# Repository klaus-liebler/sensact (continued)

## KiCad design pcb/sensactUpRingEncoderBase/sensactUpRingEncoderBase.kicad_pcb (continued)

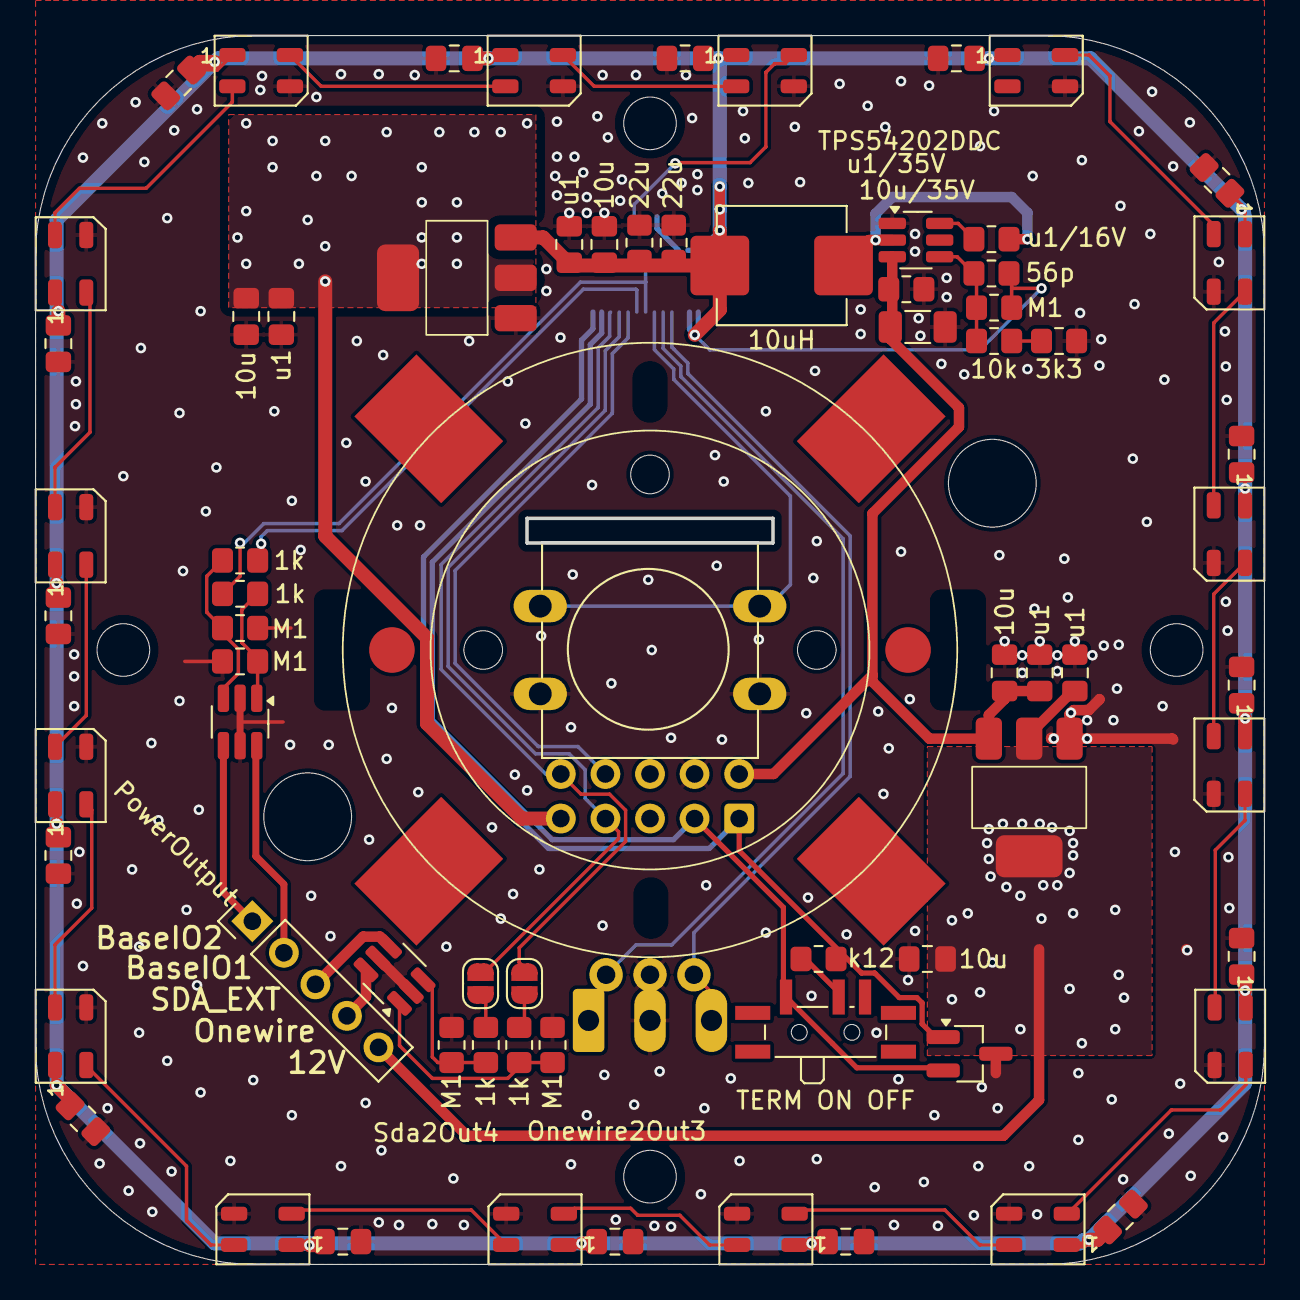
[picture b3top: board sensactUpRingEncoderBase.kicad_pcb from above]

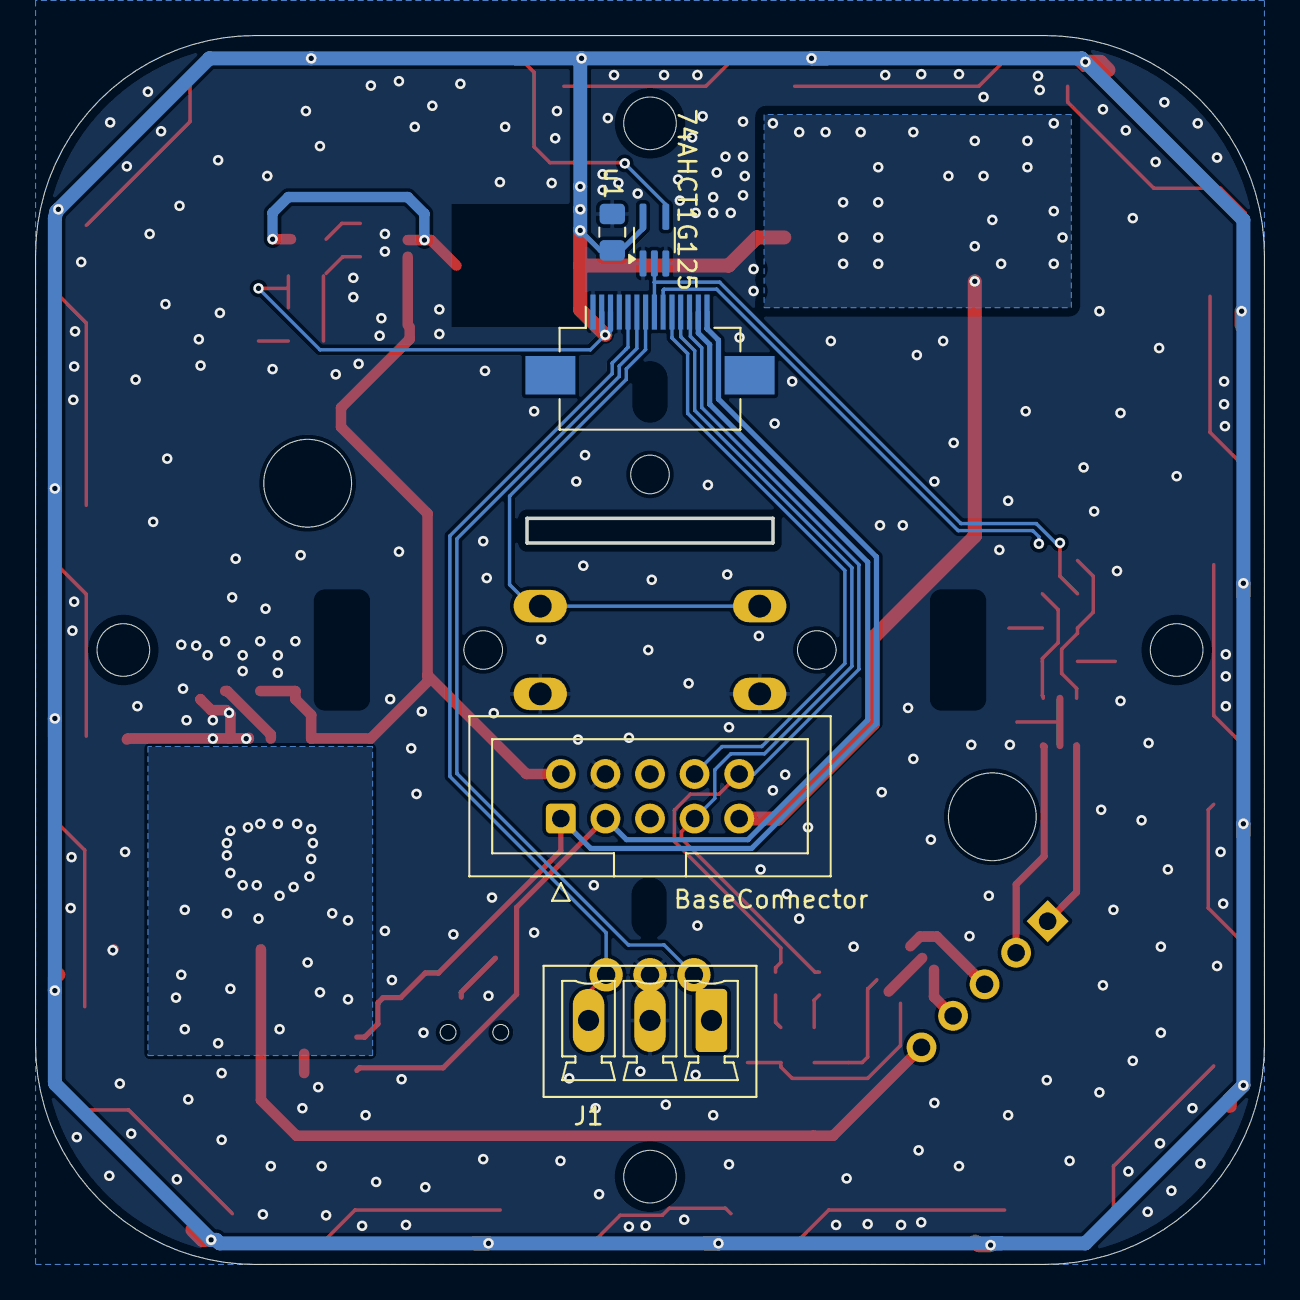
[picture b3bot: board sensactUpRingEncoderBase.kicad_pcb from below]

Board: 2 copper layers, 70.0 x 70.0 mm, 81 parts (5 on the bottom side), 46 nets.

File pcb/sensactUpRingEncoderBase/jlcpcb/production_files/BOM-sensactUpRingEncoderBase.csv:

Comment,Designator,Footprint,LCSC,Quantity
AMS1117-12,U7,SOT-223-3_TabPin2_HANDSOLDER,,1
ROT_EXT,J1,"PhoenixContact_MCV_1,5_3-G-3.5_1x03_P3.50mm_Vertical_smallerCourtyard",,1
10u,C55,C_0805_2012Metric_Pad1.18x1.45mm_HandSolder,,1
u1,C54,C_0805_2012Metric_Pad1.18x1.45mm_HandSolder,,1
u1,C53,C_0805_2012Metric_Pad1.18x1.45mm_HandSolder,,1
10u,C48,C_0805_2012Metric_Pad1.18x1.45mm_HandSolder,,1
BaseConnector,J3,IDC-Header_2x05_P2.54mm_Vertical,,1
AMS1117-3.3,U4,SOT-223-3_TabPin2_HANDSOLDER,,1
M1,R61,R_0805_2012Metric_Pad1.20x1.40mm_HandSolder,,1
M1,R62,R_0805_2012Metric_Pad1.20x1.40mm_HandSolder,,1
MountingHole,H5,MountingHole_2.2mm_M2,,1
SW_Push,SW1,Button_12mm_ANCHOR_CENTER,,1
u1,C15,C_0805_2012Metric_Pad1.18x1.45mm_HandSolder,,1
M1,R64,R_0805_2012Metric_Pad1.20x1.40mm_HandSolder,,1
u1,C20,C_0805_2012Metric_Pad1.18x1.45mm_HandSolder,,1
TERM ON OFF,SW2,SW_SPDT_PCM12_handsolder,,1
NUP2105L,D1,SOT-23_Handsoldering,,1
WS2812B,D6,LED_WS2812B-Mini_PLCC4_3.5x3.5mm,,1
MountingHole,H4,MountingHole_2.2mm_M2,,1
WS2812B,D12,LED_WS2812B-Mini_PLCC4_3.5x3.5mm,,1
MountingHole,H1,MountingHole_5mm,,1
WS2812B,D7,LED_WS2812B-Mini_PLCC4_3.5x3.5mm,,1
u1,C22,C_0805_2012Metric_Pad1.18x1.45mm_HandSolder,,1
WS2812B,D13,LED_WS2812B-Mini_PLCC4_3.5x3.5mm,,1
u1,C17,C_0805_2012Metric_Pad1.18x1.45mm_HandSolder,,1
u1/16V,C81,R_0805_2012Metric_Pad1.20x1.40mm_HandSolder,,1
u1/35V,C79,R_0805_2012Metric_Pad1.20x1.40mm_HandSolder,,1
k12,R1,R_0805_2012Metric_Pad1.20x1.40mm_HandSolder,,1
M1,R63,R_0805_2012Metric_Pad1.20x1.40mm_HandSolder,,1
3k3,R49,R_0805_2012Metric_Pad1.20x1.40mm_HandSolder,,1
WS2812B,D15,LED_WS2812B-Mini_PLCC4_3.5x3.5mm,,1
WS2812B,D4,LED_WS2812B-Mini_PLCC4_3.5x3.5mm,,1
u1,C23,C_0805_2012Metric_Pad1.18x1.45mm_HandSolder,,1
u1,C24,C_0805_2012Metric_Pad1.18x1.45mm_HandSolder,,1
WS2812B,D14,LED_WS2812B-Mini_PLCC4_3.5x3.5mm,,1
u1,C16,C_0805_2012Metric_Pad1.18x1.45mm_HandSolder,,1
1k,R57,R_0805_2012Metric_Pad1.20x1.40mm_HandSolder,,1
u1,C28,C_0805_2012Metric_Pad1.18x1.45mm_HandSolder,,1
22u,C84,R_0805_2012Metric_Pad1.20x1.40mm_HandSolder,,1
AO6800-HXY,Q3,SOT-23-6_Handsoldering,,1
WS2812B,D10,LED_WS2812B-Mini_PLCC4_3.5x3.5mm,,1
u1,C26,C_0805_2012Metric_Pad1.18x1.45mm_HandSolder,,1
PowerOutput,J7,PinHeader_1x05_P2.54mm_Vertical,,1
u1,C27,C_0805_2012Metric_Pad1.18x1.45mm_HandSolder,,1
WS2812B,D5,LED_WS2812B-Mini_PLCC4_3.5x3.5mm,,1
10u,C12,C_0805_2012Metric_Pad1.18x1.45mm_HandSolder,,1
u1,C29,C_0805_2012Metric_Pad1.18x1.45mm_HandSolder,,1
WS2812B,D16,LED_WS2812B-Mini_PLCC4_3.5x3.5mm,,1
MountingHole,H2,MountingHole_5mm,,1
WS2812B,D17,LED_WS2812B-Mini_PLCC4_3.5x3.5mm,,1
10uH,L4,L_0630,,1
WS2812B,D9,LED_WS2812B-Mini_PLCC4_3.5x3.5mm,,1
MountingHole,H3,MountingHole_2.2mm_M2,,1
u1,C10,C_0805_2012Metric_Pad1.18x1.45mm_HandSolder,,1
WS2812B,D8,LED_WS2812B-Mini_PLCC4_3.5x3.5mm,,1
56p,C82,R_0805_2012Metric_Pad1.20x1.40mm_HandSolder,,1
u1,C21,C_0805_2012Metric_Pad1.18x1.45mm_HandSolder,,1
WS2812B,D2,LED_WS2812B-Mini_PLCC4_3.5x3.5mm,,1
10u/35V,C80,C_1206_3216Metric_Pad1.33x1.80mm_HandSolder,,1
AO6800-HXY,Q2,SOT-23-6_Handsoldering,,1
WS2812B,D3,LED_WS2812B-Mini_PLCC4_3.5x3.5mm,,1
10u,C9,C_0805_2012Metric_Pad1.18x1.45mm_HandSolder,,1
u1,C11,C_0805_2012Metric_Pad1.18x1.45mm_HandSolder,,1
u1,C18,C_0805_2012Metric_Pad1.18x1.45mm_HandSolder,,1
WS2812B,D11,LED_WS2812B-Mini_PLCC4_3.5x3.5mm,,1
u1,C14,C_0805_2012Metric_Pad1.18x1.45mm_HandSolder,,1
10k,R60,R_0805_2012Metric_Pad1.20x1.40mm_HandSolder,,1
22u,C83,R_0805_2012Metric_Pad1.20x1.40mm_HandSolder,,1
1k,R56,R_0805_2012Metric_Pad1.20x1.40mm_HandSolder,,1
M1,R59,R_0805_2012Metric_Pad1.20x1.40mm_HandSolder,,1
u1,C19,C_0805_2012Metric_Pad1.18x1.45mm_HandSolder,,1
1k,R58,R_0805_2012Metric_Pad1.20x1.40mm_HandSolder,,1
TPS54202DDC,U27,SOT-23-6_Handsoldering,,1
1k,R55,R_0805_2012Metric_Pad1.20x1.40mm_HandSolder,,1
RotaryEncoder,SW3,Encoder Alps-Alpine EC35,,1
u1,C25,C_0805_2012Metric_Pad1.18x1.45mm_HandSolder,,1
u1,C13,C_0805_2012Metric_Pad1.18x1.45mm_HandSolder,,1
ToBase,J5,Hirose_FH12-14S-0.5SH_1x14-1MP_P0.50mm_Horizontal_handsolder,,1
74AHCT1G125,U5,SOT-353_SC-70-5_Handsoldering,,1

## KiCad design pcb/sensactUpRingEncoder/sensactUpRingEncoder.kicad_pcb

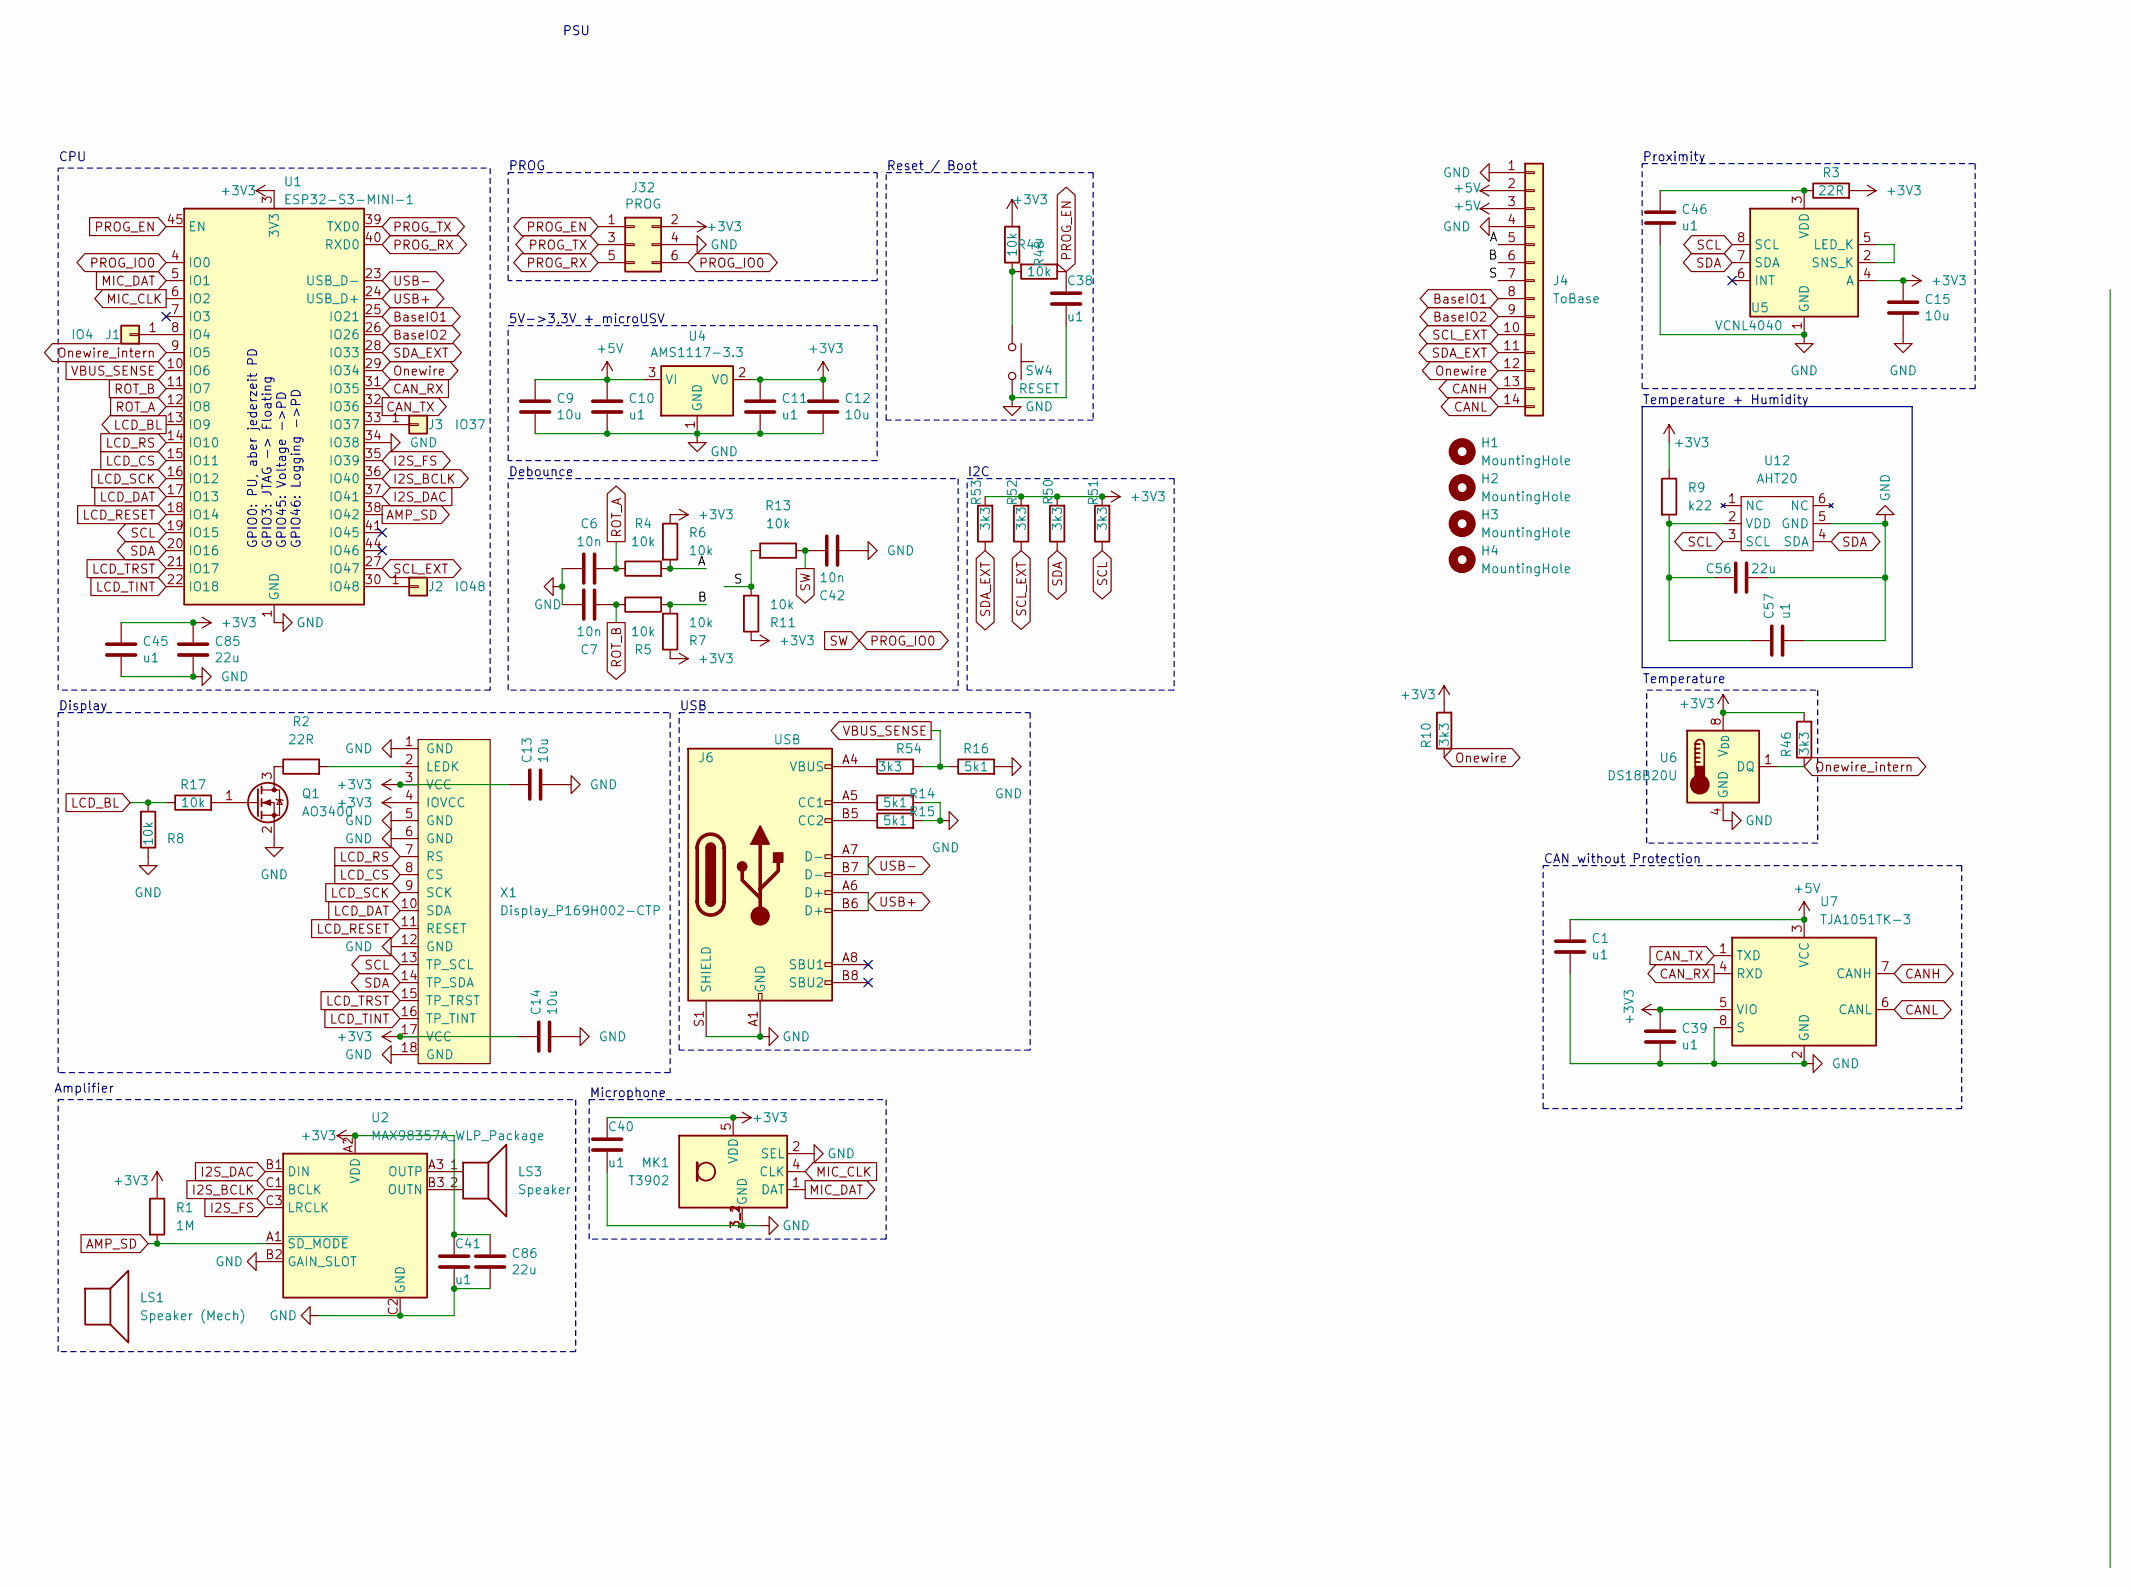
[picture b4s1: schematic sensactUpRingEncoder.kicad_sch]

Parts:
C1, C10, C11, C38, C39, C40, C41, C45, C46: u1; C_0201_0603Metric
C6, C7, C42: 10n; C_0201_0603Metric
C9, C12, C13, C14, C15: 10u; C_0402_1005Metric
C56, C85, C86: 22u; C_0603_1608Metric; MPN CL10A226MP8NUNE
C57: u1; C_0201_0603Metric; MPN GRM033R61A104KE15D
H1, H2, H3, H4: MountingHole; MountingHole_2.2mm_M2_DIN965
J1: IO4; TestPoint_THTPad_D1.0mm_Drill0.5mm
J2: IO48; TestPoint_THTPad_D1.5mm_Drill0.7mm
J3: IO37; TestPoint_THTPad_D1.5mm_Drill0.7mm
J4: ToBase; Hirose_FH12-14S-0.5SH_1x14-1MP_P0.50mm_Horizontal
J6: USB; USB_C_Receptacle_HRO_TYPE-C-31-M-12
J32: PROG; PinHeader_2x03_P1.27mm_Vertical_SMD
LS1: Speaker (Mech); SPEAKER_2415
LS3: Speaker; PinHeader_1x02_P1.27mm_Vertical
MK1: T3902; MIC_T3902
Q1: AO3400; SOT-23_smaller
R1: 1M; R_0805_2012Metric_Pad1.20x1.40mm_HandSolder
R2, R3: 22R; R_0805_2012Metric
R4, R5, R6, R7, R8, R11, R13, R17, R47, R48: 10k; R_0201_0603Metric
R9: k22; R_0805_2012Metric_Pad1.20x1.40mm_HandSolder; MPN 0402WGF2200TCE
R10, R46: 3k3; R_0402_1005Metric
R14, R15, R16: 5k1; R_0402_1005Metric
R50, R51, R52, R53, R54: 3k3; R_0402_1005Metric; MPN 0402WGF3301TCE
SW4: RESET; SW_Push_SPST_NO_4x3x2_handsolder
U1: ESP32-S3-MINI-1
U2: MAX98357A_WLP_Package; Maxim_WLP-9_1.595x1.415_Layout3x3_P0.4mm_Ball0.27mm_Pad0.25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
U4: AMS1117-3.3; SOT-223-3_TabPin2
U5: VCNL4040; VCNL4040_handsolder
U6: DS18B20U; MSOP-8_3x3mm_P0.65mm_handsolder
U7: TJA1051TK-3; HVSON-8-1EP_3x3mm_P0.65mm_EP1.6x2.4mm
U12: AHT20; AHT21; MPN AHT20
X1: Display_P169H002-CTP

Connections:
+3V3: C11.1, C12.1, C13.1, C14.1, C15.1, C39.1, C40.1, C41.1, C45.1, C85.1, C86.1, J32.2, MK1.5 (VDD), R1.1, R3.2, R6.1, R7.1, R9.1, R10.2, R11.1, R46.2, R47.2, R50.2, R51.2, R52.2, R53.2, U1.3 (3V3), U2.A2 (VDD), U4.2 (VO), U5.4 (A), U6.8 (V_{DD}), U7.5 (VIO), X1.3 (VCC), X1.4 (IOVCC), X1.17 (VCC)
+5V: C1.1, C9.1, C10.1, J4.2, J4.3, U4.3 (VI), U7.3 (VCC)
/A: J4.5, R4.2, R6.2
/B: J4.6, R5.2, R7.2
/S: J4.7, R11.2, R13.2
AMP_SD: R1.2, U1.38 (IO42), U2.A1 (~SD_MODE)
BaseIO1: J4.8, U1.25 (IO21)
BaseIO2: J4.9, U1.26 (IO26)
CANH: J4.13, U7.7 (CANH)
CANL: J4.14, U7.6 (CANL)
CAN_RX: U1.31 (IO35), U7.4 (RXD)
CAN_TX: U1.32 (IO36), U7.1 (TXD)
GND: C1.2, C6.1, C7.1, C9.2, C10.2, C11.2, C12.2, C13.2, C14.2, C15.2, C38.2, C39.2, C40.2, C41.2, C42.2, C45.2, C46.2, C56.2, C57.1, C85.2, C86.2, J4.1, J4.4, J6.A1 (GND), J6.A12 (GND), J6.B1 (GND), J6.B12 (GND), J6.S1 (SHIELD), J32.4, MK1.2 (SEL), MK1.3_1 (GND), MK1.3_2 (GND), Q1.2 (S), R8.1, R14.2, R15.2, R16.2, SW4.2, U1.1 (GND), U1.2 (GND), U1.34 (IO38), U1.42 (GND), U1.43 (GND), U1.46 (GND), U1.47 (GND), U1.48 (GND), U1.49 (GND), U1.50 (GND), U1.51 (GND), U1.52 (GND), U1.53 (GND), U1.54 (GND), U1.55 (GND), U1.56 (GND), U1.57 (GND), U1.58 (GND), U1.59 (GND), U1.60 (GND), U1.61 (GND), U1.62 (GND), U1.63 (GND), U1.64 (GND), U1.65 (GND), U2.B2 (GAIN_SLOT), U2.C2 (GND), U4.1 (GND), U5.1 (GND), U6.4 (GND), U7.2 (GND), U7.8 (S), U7.9 (GND), U12.5 (GND), X1.1 (GND), X1.5 (GND), X1.6 (GND), X1.12 (GND), X1.18 (GND)
I2S_BCLK: U1.36 (IO40), U2.C1 (BCLK)
I2S_DAC: U1.37 (IO41), U2.B1 (DIN)
I2S_FS: U1.35 (IO39), U2.C3 (LRCLK)
LCD_BL: R8.2, R17.1, U1.13 (IO9)
LCD_CS: U1.15 (IO11), X1.8 (CS)
LCD_DAT: U1.17 (IO13), X1.10 (SDA)
LCD_RESET: U1.18 (IO14), X1.11 (RESET)
LCD_RS: U1.14 (IO10), X1.7 (RS)
LCD_SCK: U1.16 (IO12), X1.9 (SCK)
LCD_TINT: U1.22 (IO18), X1.16 (TP_TINT)
LCD_TRST: U1.21 (IO17), X1.15 (TP_TRST)
MIC_CLK: MK1.4 (CLK), U1.6 (IO2)
MIC_DAT: MK1.1 (DAT), U1.5 (IO1)
unnamed: J1.1, U1.8 (IO4)
unnamed: J2.1, U1.30 (IO48)
unnamed: J3.1, U1.33 (IO37)
unnamed: J6.A5 (CC1), R14.1
unnamed: J6.B5 (CC2), R15.1
unnamed: J6.A4 (VBUS), J6.A9 (VBUS), J6.B4 (VBUS), J6.B9 (VBUS), R54.2
unnamed: Q1.3 (D), R2.1
unnamed: Q1.1 (G), R17.2
unnamed: R47.1, R48.2, SW4.1
unnamed: LS3.2, U2.B3 (OUTN)
unnamed: LS3.1, U2.A3 (OUTP)
unnamed: U5.2 (SNS_K), U5.5 (LED_K)
unnamed: C46.1, R3.1, U5.3 (VDD)
unnamed: C56.1, C57.2, R9.2, U12.2 (VDD)
unnamed: R2.2, X1.2 (LEDK)
Onewire: J4.12, R10.1, U1.29 (IO34)
Onewire_intern: R46.1, U1.9 (IO5), U6.1 (DQ)
PROG_EN: C38.1, J32.1, R48.1, U1.45 (EN)
PROG_IO0: C42.1, J32.6, R13.1, U1.4 (IO0)
PROG_RX: J32.5, U1.40 (RXD0)
PROG_TX: J32.3, U1.39 (TXD0)
ROT_A: C6.2, R4.1, U1.12 (IO8)
ROT_B: C7.2, R5.1, U1.11 (IO7)
SCL: R51.1, U1.19 (IO15), U5.8 (SCL), U12.3 (SCL), X1.13 (TP_SCL)
SCL_EXT: J4.10, R52.1, U1.27 (IO47)
SDA: R50.1, U1.20 (IO16), U5.7 (SDA), U12.4 (SDA), X1.14 (TP_SDA)
SDA_EXT: J4.11, R53.1, U1.28 (IO33)
USB+: J6.A6 (D+), J6.B6 (D+), U1.24 (USB_D+)
USB-: J6.A7 (D-), J6.B7 (D-), U1.23 (USB_D-)
VBUS_SENSE: R16.1, R54.1, U1.10 (IO6)

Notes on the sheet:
CAN without Protection
Temperature
Proximity
Reset / Boot
Temperature + Humidity
Amplifier
USB
5V->3,3V + microUSV
Debounce
Display
CPU
PSU
I2C
GPIO0: PU, aber jederzeit PD GPIO3: JTAG -> Floating GPIO45: Voltage ->PD GPIO46: Logging ->PD
Microphone
PROG

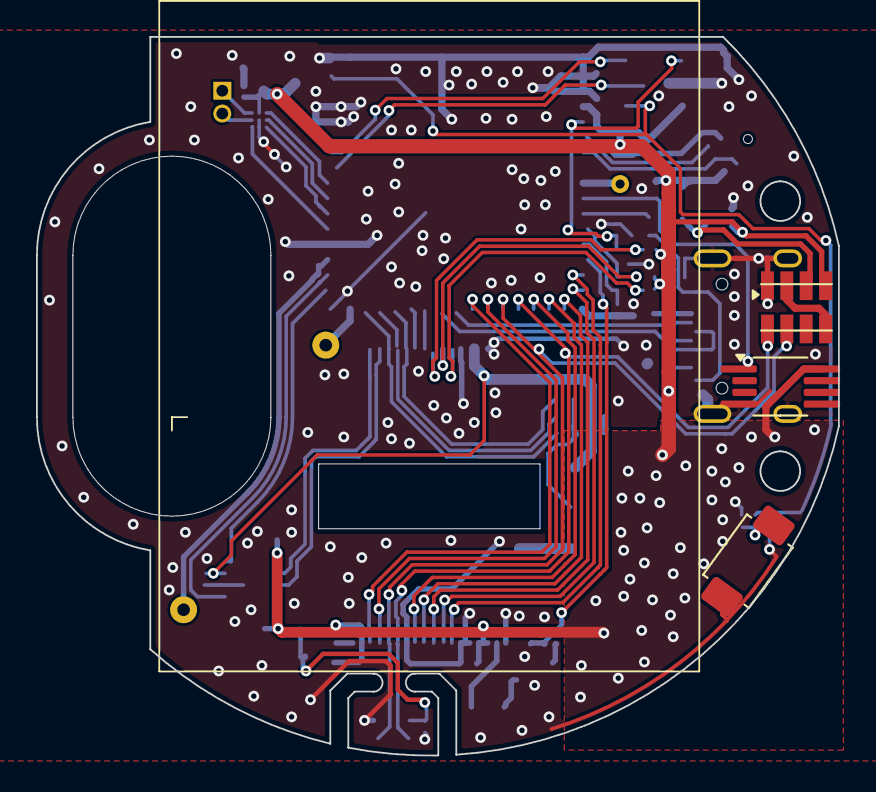
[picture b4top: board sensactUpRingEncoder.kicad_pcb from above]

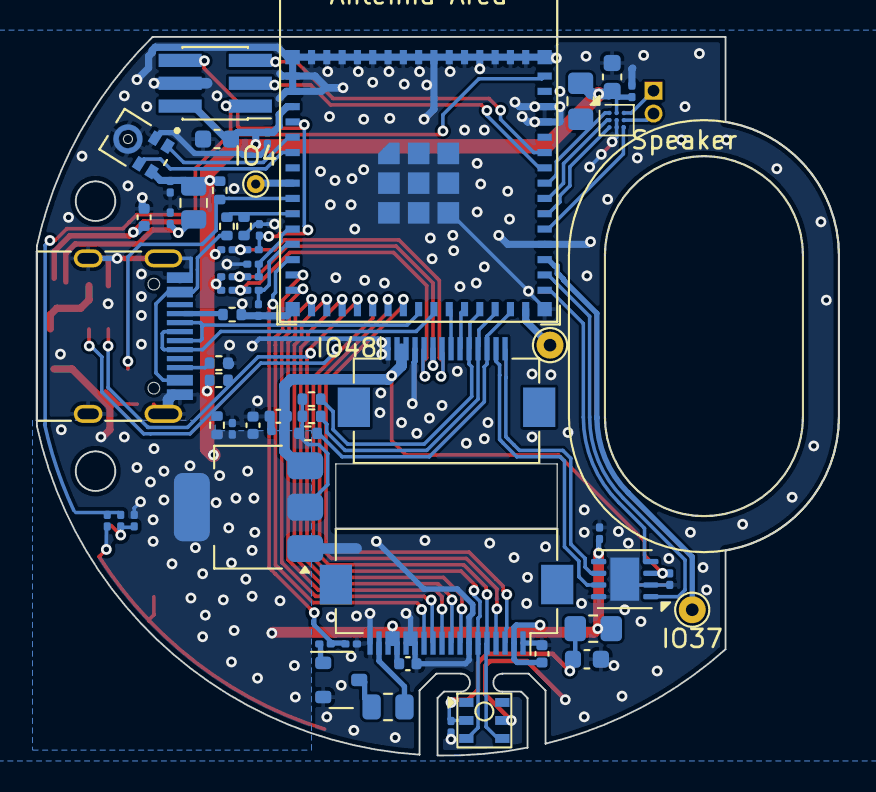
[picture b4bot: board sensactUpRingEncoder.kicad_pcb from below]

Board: 2 copper layers, 44.6 x 39.9 mm, 68 parts (61 on the bottom side), 56 nets.

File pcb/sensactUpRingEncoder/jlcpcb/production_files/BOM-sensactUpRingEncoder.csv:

Comment,Designator,Footprint,LCSC,Quantity
5k1,"R14,R15,R16",R_0402_1005Metric,C105872,3
10k,"R11,R13,R17,R4,R47,R48,R5,R6,R7,R8",R_0201_0603Metric,C106225,10
3k3,"R10,R46,R50,R51,R52,R53,R54",R_0402_1005Metric,C137992,7
USB,J6,USB_C_Receptacle_HRO_TYPE-C-31-M-12,C165948,1
22R,"R2,R3",R_0805_2012Metric,C17561,2
MAX98357A_WLP_Package,U2,Maxim_WLP-9_1.595x1.415_Layout3x3_P0.4mm_Ball0.27mm_Pad0.25mm_NSMD,C2682619,1
ToBase,J4,Hirose_FH12-14S-0.5SH_1x14-1MP_P0.50mm_Horizontal,C2856800,1
Display_P169H002-CTP,X1,Display_P169H002-CTP,C2856802,1
TJA1051TK-3,U7,HVSON-8-1EP_3x3mm_P0.65mm_EP1.6x2.4mm,C2875699,1
ESP32-S3-MINI-1,U1,ESP32-S3-MINI-1,C2913206,1
AHT20,U12,AHT21,C3012622,1
10u,"C12,C13,C14,C15,C9",C_0402_1005Metric,C315248,5
T3902,MK1,MIC_T3902,C3171752,1
AO3400,Q1,SOT-23_smaller,C347475,1
PROG,J32,PinHeader_2x03_P1.27mm_Vertical_SMD,C3975186,1
AMS1117-3.3,U4,SOT-223-3_TabPin2,C6186,1
u1,"C1,C10,C11,C38,C39,C40,C41,C45,C46,C57",C_0201_0603Metric,C76934,10
10n,"C42,C6,C7",C_0201_0603Metric,C76941,3
22u,"C56,C85,C86",C_0603_1608Metric,C86295,3
DS18B20U,U6,MSOP-8_3x3mm_P0.65mm_handsolder,,1
RESET,SW4,SW_Push_SPST_NO_4x3x2_handsolder,,1
VCNL4040,U5,VCNL4040_handsolder,,1

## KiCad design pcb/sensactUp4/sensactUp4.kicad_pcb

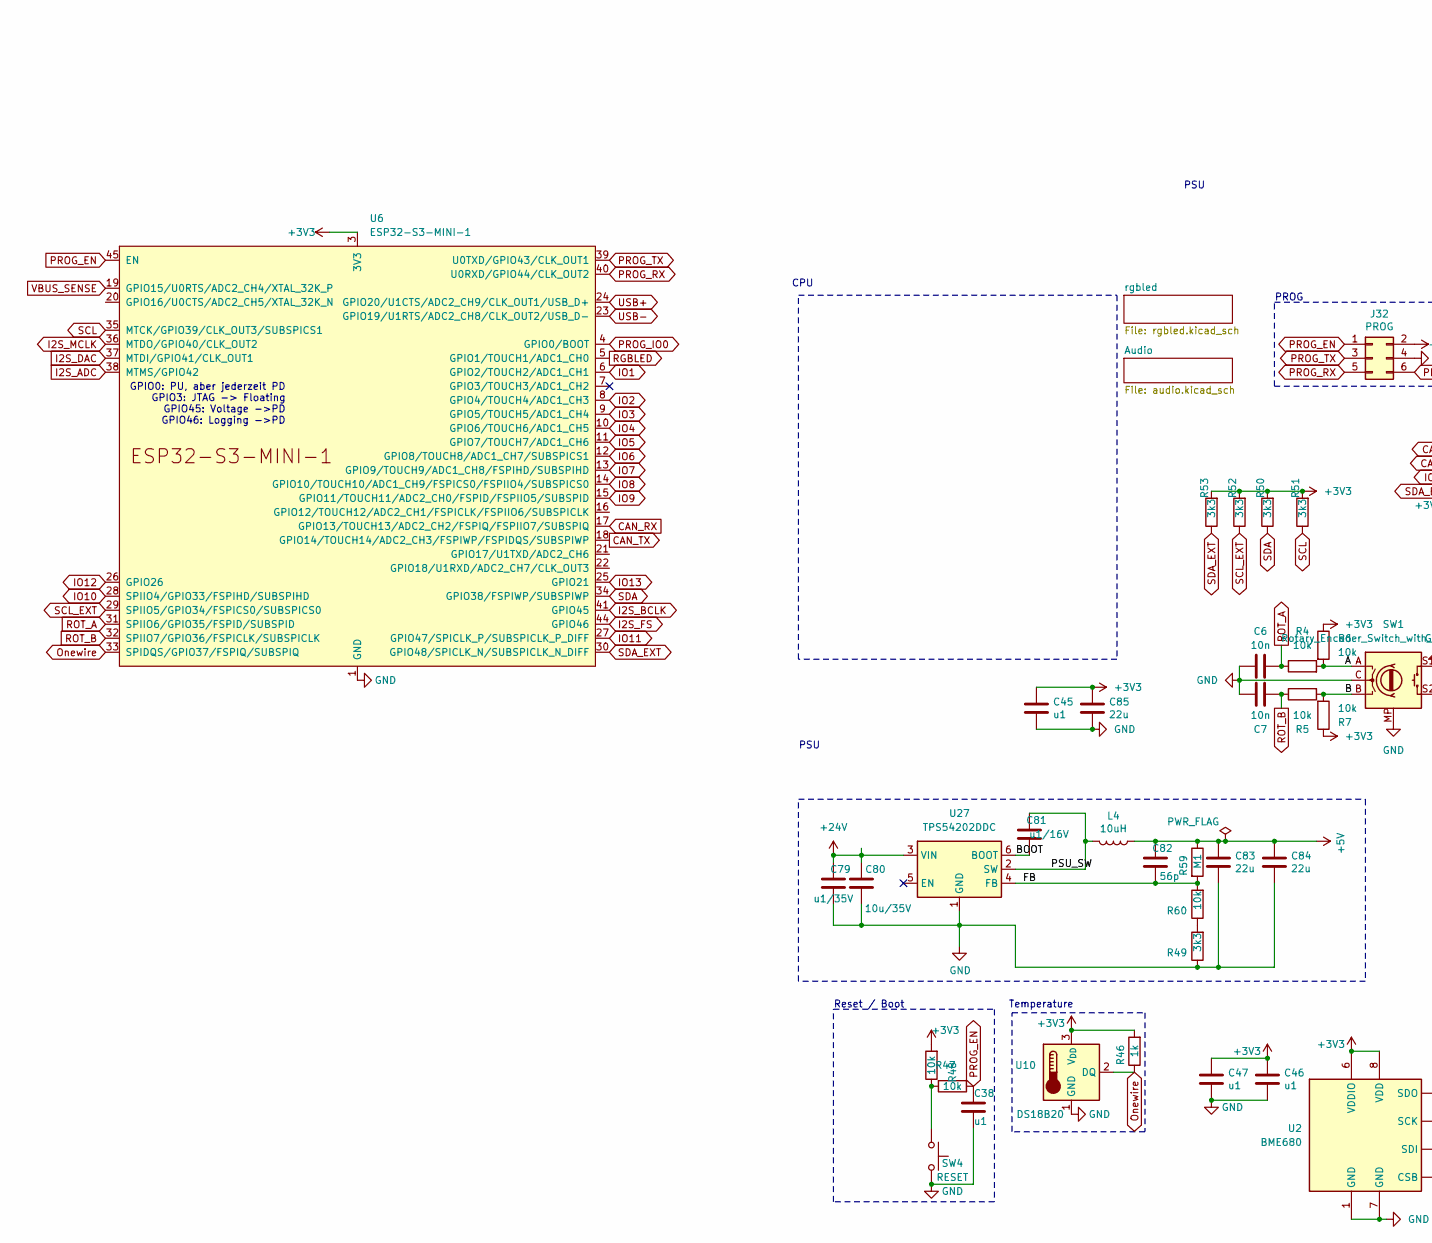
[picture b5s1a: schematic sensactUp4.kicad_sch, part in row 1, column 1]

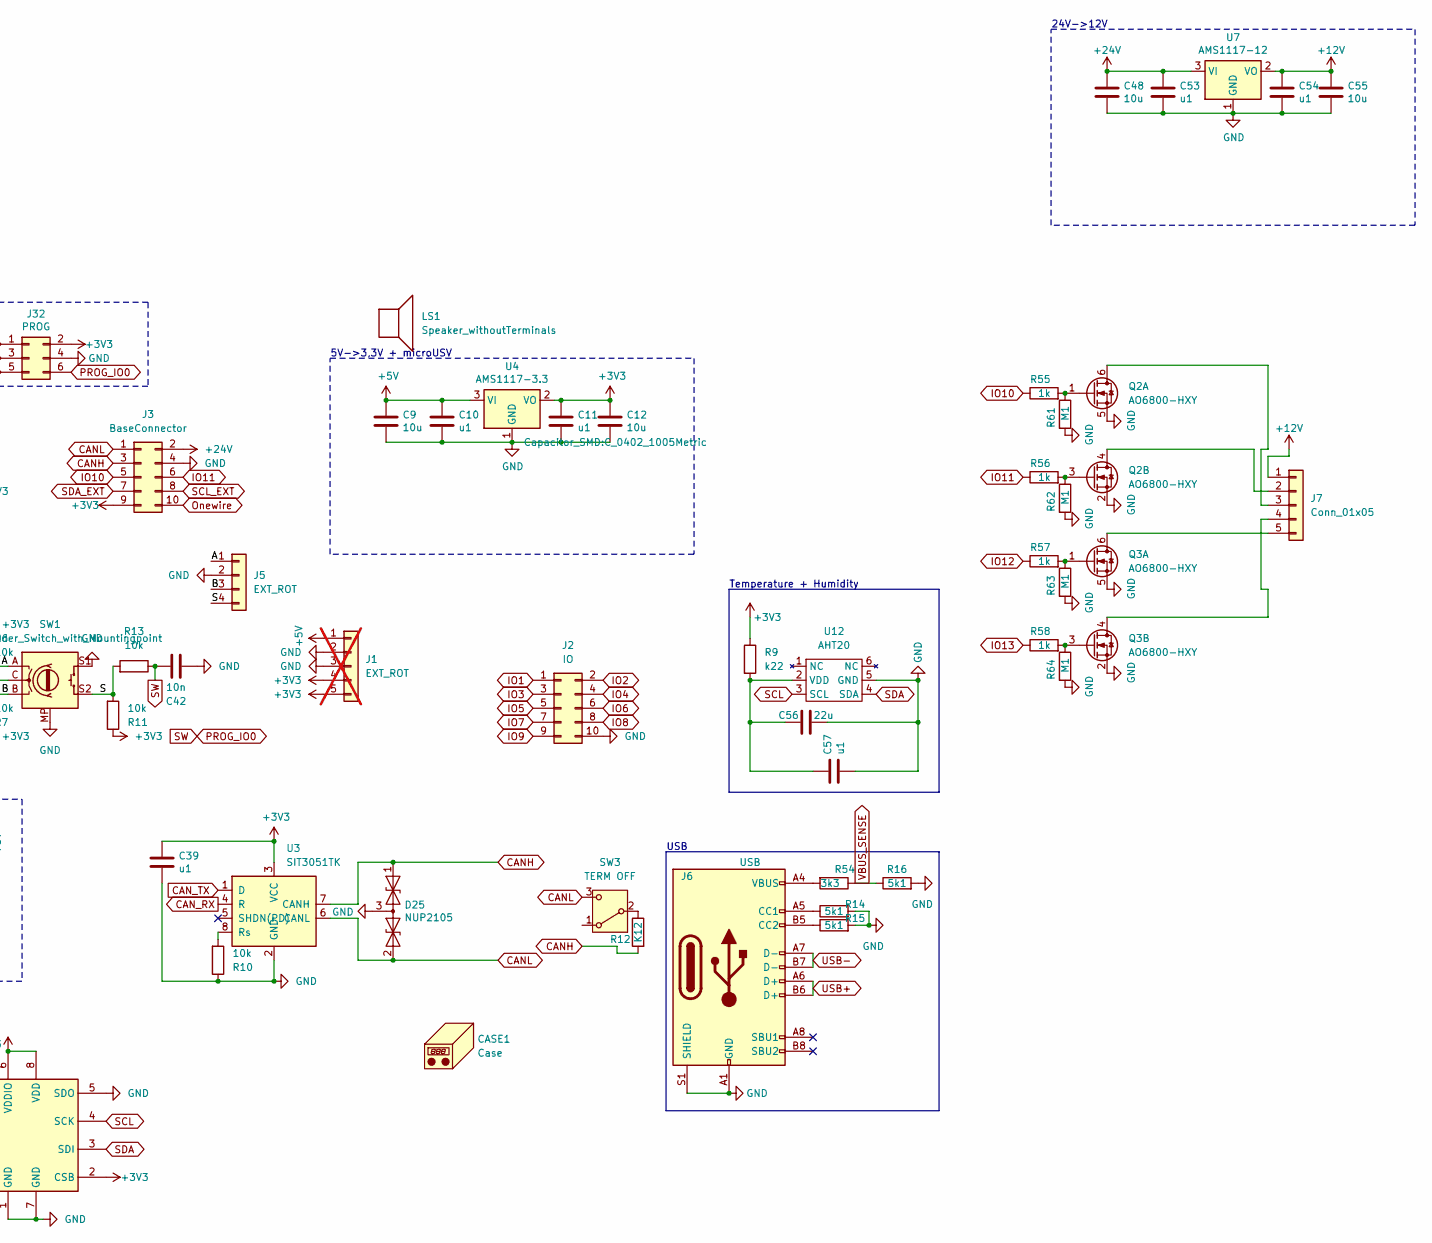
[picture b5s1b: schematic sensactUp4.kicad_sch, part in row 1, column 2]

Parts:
C6, C7, C42: 10n; C_0201_0603Metric
C9, C12: 10u; C_0402_1005Metric
C10, C11, C38, C39, C45, C46, C47: u1; C_0201_0603Metric
C48, C55: 10u; C_0805_2012Metric_Pad1.18x1.45mm_HandSolder
C53, C54: u1; C_0805_2012Metric_Pad1.18x1.45mm_HandSolder
C56, C83, C84, C85: 22u; C_0603_1608Metric; MPN CL10A226MP8NUNE
C57: u1; C_0201_0603Metric; MPN GRM033R61A104KE15D
C79: u1/35V; C_0603_1608Metric; MPN CC0603KRX7R9BB104
C80: 10u/35V; C_0805_2012Metric; MPN CGA0805X5R106K350MT
C81: u1/16V; C_0201_0603Metric; MPN CC0603KRX7R9BB104
C82: 56p; C_0201_0603Metric; MPN CC0402JRNPO9BN560
CASE1: Case; KiCad-Logo_5mm_SilkScreen
D25: NUP2105; SOT-23_Handsoldering; MPN NUP2105L
J1: EXT_ROT; PinHeader_1x05_P2.54mm_Vertical; not fitted
J2: IO; PinHeader_2x05_P2.54mm_Vertical
J3: BaseConnector; IDC-Header_2x05_P2.54mm_Vertical
J5: EXT_ROT; PhoenixContact_MCV_1,5_4-G-3.5_1x04_P3.50mm_Vertical
J6: USB; GT-USB-7051A
J7: Conn_01x05; PinHeader_1x05_P2.54mm_Vertical
J32: PROG; PinHeader_2x03_P2.54mm_Vertical
L4: 10uH; L_Abracon_ASPI-0630LR; MPN FXL0630-100-M
LS1: Speaker_withoutTerminals; SPEAKER_2415
Q2, Q3: AO6800-HXY; SOT-23-6
R4, R5, R6, R7, R10, R11, R13, R47, R48: 10k; R_0201_0603Metric
R9: k22; R_0402_1005Metric; MPN 0402WGF2200TCE
R12: K12; R_1206_3216Metric_Pad1.30x1.75mm_HandSolder; MPN 1206W4F1200T5E
R14, R15, R16: 5k1; R_0402_1005Metric
R46, R55, R56, R57, R58: 1k; R_0402_1005Metric
R49, R50, R51, R52, R53, R54: 3k3; R_0402_1005Metric; MPN 0402WGF3301TCE
R59, R61, R62, R63, R64: M1; R_0201_0603Metric; MPN 0201WMF1003TEE
R60: 10k; R_0201_0603Metric; MPN 0201WMF1002TEE
SW1: Rotary_Encoder_Switch_with_Mountingpoint; RotaryEncoder_Alps_EC11E-Switch_Vertical_H20mm
SW3: TERM OFF; Switch_SS12D00
SW4: RESET; SW_SPST_TL3342_smaller_handsolder
U2: BME680; Bosch_LGA-8_3x3mm_P0.8mm_ClockwisePinNumbering
U3: SIT3051TK; DFN-8-1EP_3x3mm_P0.65mm_EP1.55x2.4mm
U4: AMS1117-3.3; SOT-223-3_TabPin2
U6: ESP32-S3-MINI-1
U7: AMS1117-12; SOT-223-3_TabPin2_HANDSOLDER
U10: DS18B20; TO-92L_HandSolder
U12: AHT20; AHT21; MPN AHT20
U27: TPS54202DDC; SOT-23-6_Handsoldering; MPN TPS54202DDCR

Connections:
+3V3: C11.1, C12.1, C39.1, C45.1, C46.1, C47.1, C85.1, J1.4, J1.5, J3.9, J32.2, R6.1, R7.1, R9.1, R11.1, R46.2, R47.2, R50.2, R51.2, R52.2, R53.2, U2.2 (CSB), U2.6 (VDDIO), U2.8 (VDD), U3.3 (VCC), U4.2 (VO), U6.3 (3V3), U10.3 (V_{DD}); also elsewhere on the board
+5V: C9.1, C10.1, C82.2, C83.1, C84.1, J1.1, L4.1, R59.1, U4.3 (VI); also elsewhere on the board
+12V: C54.1, C55.1, J7.1, U7.2 (VO)
+24V: C48.1, C53.1, C79.2, C80.2, J3.2, U7.3 (VI), U27.3 (VIN)
/A: J5.1, R4.2, R6.2, SW1.A
/B: J5.3, R5.2, R7.2, SW1.B
/BOOT: C81.1, U27.6 (BOOT)
/FB: C82.1, R59.2, R60.2, U27.4 (FB)
/PSU_SW: C81.2, L4.2, U27.2 (SW)
/S: J5.4, R11.2, R13.2, SW1.S2
CANH: D25.1 (A1), J3.3, R12.2, U3.7 (CANH)
CANL: D25.2 (A2), J3.1, SW3.3 (C), U3.6 (CANL)
CAN_RX: U3.4 (R), U6.17 (GPIO13/TOUCH13/ADC2_CH2/FSPIQ/FSPIIO7/S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)
CAN_TX: U3.1 (D), U6.18 (GPIO14/TOUCH14/ADC2_CH3/FSPIWP/FSPIDQS/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)
GND: C6.1, C7.1, C9.2, C10.2, C11.2, C12.2, C38.2, C39.2, C42.2, C45.2, C46.2, C47.2, C48.2, C53.2, C54.2, C55.2, C56.2, C57.1, C79.1, C80.1, C83.2, C84.2, C85.2, D25.3 (common), J1.2, J1.3, J2.10, J3.4, J5.2, J6.A1 (GND), J6.A12 (GND), J6.B1 (GND), J6.B12 (GND), J6.S1 (SHIELD), J32.4, Q2.2 (S), Q2.5 (S), Q3.2 (S), Q3.5 (S), R10.1, R14.2, R15.2, R16.2, R49.1, R61.2, R62.2, R63.2, R64.2, SW1.C, SW1.MP, SW1.S1, SW4.2, U2.1 (GND), U2.5 (SDO), U2.7 (GND), U3.2 (GND), U3.9 (PAD), U4.1 (GND), U6.1 (GND), U6.2 (GND), U6.42 (GND), U6.43 (GND), U6.46 (GND), U6.47 (GND), U6.48 (GND), U6.49 (GND), U6.50 (GND), U6.51 (GND), U6.52 (GND), U6.53 (GND), U6.54 (GND), U6.55 (GND), U6.56 (GND), U6.57 (GND), U6.58 (GND), U6.59 (GND), U6.60 (GND), U6.61 (GND), U6.62 (GND), U6.63 (GND), U6.64 (GND), U6.65 (GND), U7.1 (GND), U10.1 (GND), U12.5 (GND), U27.1 (GND); also elsewhere on the board
I2S_ADC: U6.38 (MTMS/GPIO42); also elsewhere on the board
I2S_BCLK: U6.41 (GPIO45); also elsewhere on the board
I2S_DAC: U6.37 (MTDI/GPIO41/CLK_OUT1); also elsewhere on the board
I2S_FS: U6.44 (GPIO46); also elsewhere on the board
I2S_MCLK: U6.36 (MTDO/GPIO40/CLK_OUT2); also elsewhere on the board
IO1: J2.1, U6.6 (GPIO2/TOUCH2/ADC1_CH1)
IO2: J2.2, U6.8 (GPIO4/TOUCH4/ADC1_CH3)
IO3: J2.3, U6.9 (GPIO5/TOUCH5/ADC1_CH4)
IO4: J2.4, U6.10 (GPIO6/TOUCH6/ADC1_CH5)
IO5: J2.5, U6.11 (GPIO7/TOUCH7/ADC1_CH6)
IO6: J2.6, U6.12 (GPIO8/TOUCH8/ADC1_CH7/SUBSPICS1)
IO7: J2.7, U6.13 (GPIO9/TOUCH9/ADC1_CH8/FSPIHD/SUBSPIHD)
IO8: J2.8, U6.14 (GPIO10/TOUCH10/ADC1_CH9/FSPICS0/FSPIIO4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)
IO9: J2.9, U6.15 (GPIO11/TOUCH11/ADC2_CH0/FSPID/FSPIIO5/S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)
IO10: J3.5, R55.1, U6.28 (SPIIO4/GPIO33/FSPIHD/SUBSPIHD)
IO11: J3.6, R56.1, U6.27 (GPIO47/SPICLK_P/SUBSPICLK_P_DIFF)
IO12: R57.1, U6.26 (GPIO26)
IO13: R58.1, U6.25 (GPIO21)
unnamed: J6.A5 (CC1), R14.1
unnamed: J6.B5 (CC2), R15.1
unnamed: J6.A4 (VBUS), J6.A9 (VBUS), J6.B4 (VBUS), J6.B9 (VBUS), R54.2
unnamed: J7.2, Q2.4 (D)
unnamed: J7.3, Q2.6 (D)
unnamed: J7.4, Q3.4 (D)
unnamed: J7.5, Q3.6 (D)
unnamed: Q2.1 (G), R55.2, R61.1
unnamed: Q2.3 (G), R56.2, R62.1
unnamed: Q3.1 (G), R57.2, R63.1
unnamed: Q3.3 (G), R58.2, R64.1
unnamed: R47.1, R48.2, SW4.1
unnamed: R49.2, R60.1
unnamed: R12.1, SW3.2 (B)
unnamed: R10.2, U3.8 (Rs)
unnamed: C56.1, C57.2, R9.2, U12.2 (VDD)
Onewire: J3.10, R46.1, U6.33 (SPIDQS/GPIO37/FSPIQ/SUBSPIQ), U10.2 (DQ)
PROG_EN: C38.1, J32.1, R48.1, U6.45 (EN)
PROG_IO0: C42.1, J32.6, R13.1, U6.4 (GPIO0/BOOT)
PROG_RX: J32.5, U6.40 (U0RXD/GPIO44/CLK_OUT2)
PROG_TX: J32.3, U6.39 (U0TXD/GPIO43/CLK_OUT1)
RGBLED: U6.5 (GPIO1/TOUCH1/ADC1_CH0); also elsewhere on the board
ROT_A: C6.2, R4.1, U6.31 (SPIIO6/GPIO35/FSPID/SUBSPID)
ROT_B: C7.2, R5.1, U6.32 (SPIIO7/GPIO36/FSPICLK/SUBSPICLK)
SCL: R51.1, U2.4 (SCK), U6.35 (MTCK/GPIO39/CLK_OUT3/SUBSPICS1), U12.3 (SCL); also elsewhere on the board
SCL_EXT: J3.8, R52.1, U6.29 (SPIIO5/GPIO34/FSPICS0/SUBSPICS0)
SDA: R50.1, U2.3 (SDI), U6.34 (GPIO38/FSPIWP/SUBSPIWP), U12.4 (SDA); also elsewhere on the board
SDA_EXT: J3.7, R53.1, U6.30 (GPIO48/SPICLK_N/SUBSPICLK_N_DIFF)
USB+: J6.A6 (D+), J6.B6 (D+), U6.24 (GPIO20/U1CTS/ADC2_CH9/CLK_OUT1/USB_D+)
USB-: J6.A7 (D-), J6.B7 (D-), U6.23 (GPIO19/U1RTS/ADC2_CH8/CLK_OUT2/USB_D-)
VBUS_SENSE: R16.1, R54.1, U6.19 (GPIO15/U0RTS/ADC2_CH4/XTAL_32K_P)

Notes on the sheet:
Temperature
Reset / Boot
Temperature + Humidity
USB
5V->3,3V + microUSV
CPU
PSU
24V->12V
GPIO0: PU, aber jederzeit PD GPIO3: JTAG -> Floating GPIO45: Voltage ->PD GPIO46: Logging ->PD
PROG
